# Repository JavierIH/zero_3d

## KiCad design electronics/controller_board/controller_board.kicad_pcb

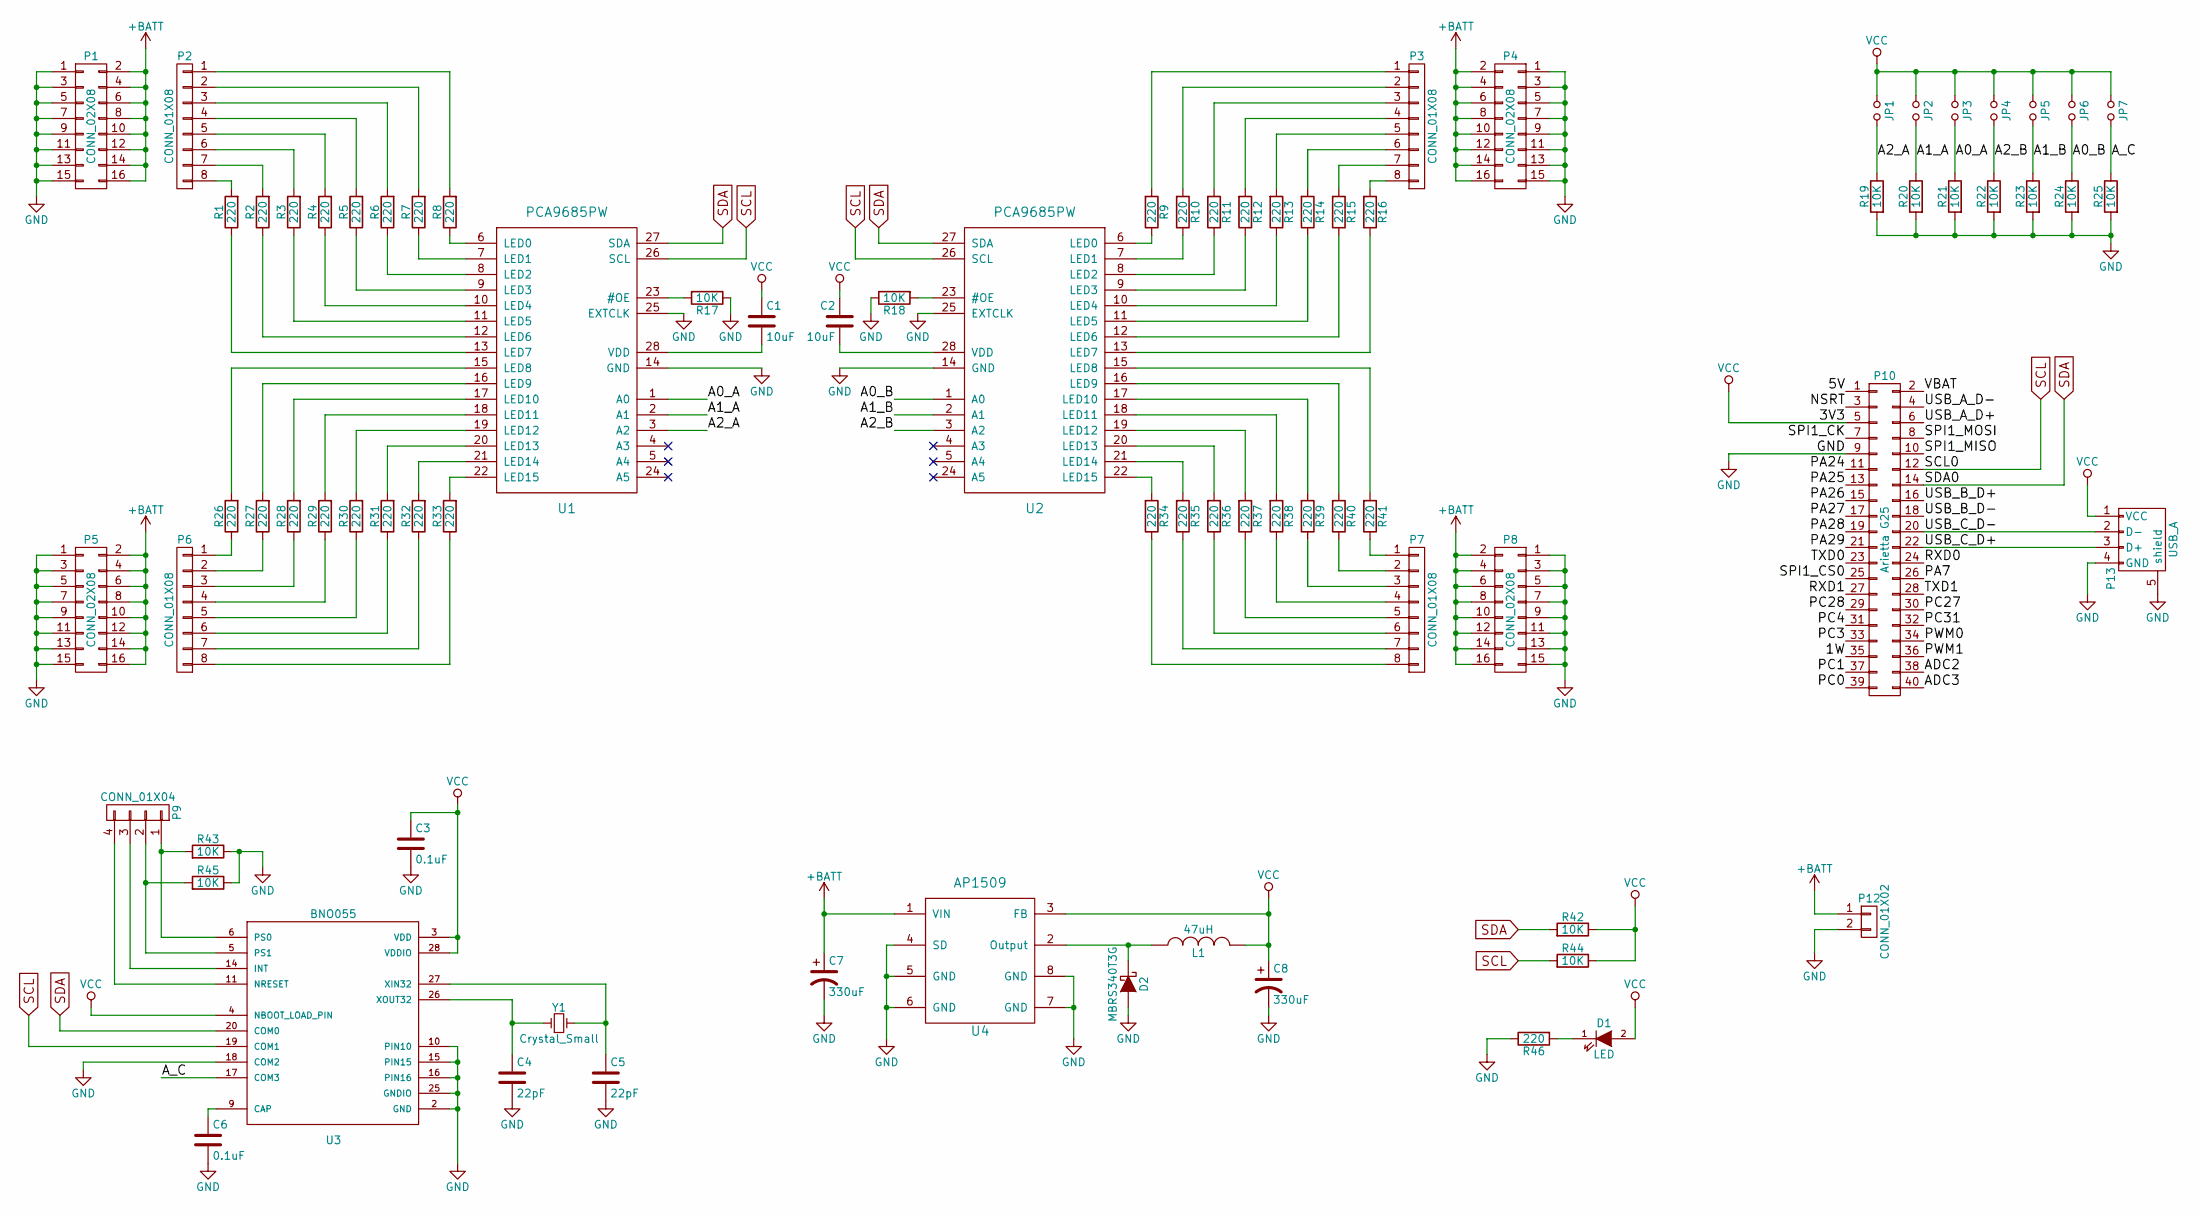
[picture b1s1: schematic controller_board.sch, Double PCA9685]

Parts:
C1, C2: 10uF; C_0603_HandSoldering
C3, C6: 0.1uF; C_0603_HandSoldering
C4, C5: 22pF; C_0603_HandSoldering
C7, C8: 330uF; c_elec_10x10
D1: LED; LED_0603
D2: MBRS340T3G; DO-214AB_Handsoldering
JP1, JP2, JP3, JP4, JP5, JP6, JP7: Jumper_NO_Small; TantalC_SizeS_EIA-3216
L1: 47uH; Choke_SMD_12x12mm_h8mm
P1, P4, P5, P8: CONN_02X08; Pin_Header_Straight_2x08
P2, P3, P6, P7: CONN_01X08; Pin_Header_Straight_1x08
P9: CONN_01X04; Pin_Header_Straight_1x04
P10: Arietta G25; Pin_Header_Straight_2x20
P12: CONN_01X02; Pin_Header_Straight_1x02
P13: USB_A; USB_A_Vertical
R1, R2, R3, R4, R5, R6, R7, R8, R9, R10, R11, R12, R13, R14, R15, R16, R26, R27, R28, R29, R30, R31, R32, R33, R34, R35, R36, R37, R38, R39, R40, R41, R46: 220; R_0603_HandSoldering
R17, R18, R19, R20, R21, R22, R23, R24, R25, R42, R43, R44, R45: 10K; R_0603_HandSoldering
U1, U2: PCA9685PW; TSSOP-28_4.4x9.7mm_Pitch0.65mm
U3: BNO055; DFN-18-1EP_4x5mm_Pitch0.5mm
U4: AP1509; SOIC-8_3.9x4.9mm_Pitch1.27mm
Y1: Crystal_Small; Crystal_HC49-SD_SMD

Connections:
+BATT: C7.1, P1.2, P1.4, P1.6, P1.8, P1.10, P1.12, P1.14, P1.16, P4.2, P4.4, P4.6, P4.8, P4.10, P4.12, P4.14, P4.16, P5.2, P5.4, P5.6, P5.8, P5.10, P5.12, P5.14, P5.16, P8.2, P8.4, P8.6, P8.8, P8.10, P8.12, P8.14, P8.16, P12.1, U4.1 (VIN)
/1W: P10.35
/5V: P10.1
/A0_A: JP3.2, R21.1, U1.1 (A0)
/A0_B: JP6.2, R24.1, U2.1 (A0)
/A1_A: JP2.2, R20.1, U1.2 (A1)
/A1_B: JP5.2, R23.1, U2.2 (A1)
/A2_A: JP1.2, R19.1, U1.3 (A2)
/A2_B: JP4.2, R22.1, U2.3 (A2)
/ADC2: P10.38
/ADC3: P10.40
/A_C: JP7.2, R25.1, U3.17 (COM3)
/NSRT: P10.3
/PA7: P10.26
/PA24: P10.11
/PA25: P10.13
/PA26: P10.15
/PA27: P10.17
/PA28: P10.19
/PA29: P10.21
/PC0: P10.39
/PC1: P10.37
/PC3: P10.33
/PC4: P10.31
/PC27: P10.30
/PC28: P10.29
/PC31: P10.32
/PWM0: P10.34
/PWM1: P10.36
/RXD0: P10.24
/RXD1: P10.27
/SPI1_CK: P10.7
/SPI1_CS0: P10.25
/SPI1_MISO: P10.10
/SPI1_MOSI: P10.8
/TXD0: P10.23
/TXD1: P10.28
/USB_A_D+: P10.6
/USB_A_D-: P10.4
/USB_B_D+: P10.16
/USB_B_D-: P10.18
/USB_C_D+: P10.22, P13.3 (D+)
/USB_C_D-: P10.20, P13.2 (D-)
/VBAT: P10.2
GND: C3.2, C4.2, C5.2, C6.2, C7.2, C8.2, D2.2 (A), P1.1, P1.3, P1.5, P1.7, P1.9, P1.11, P1.13, P1.15, P4.1, P4.3, P4.5, P4.7, P4.9, P4.11, P4.13, P4.15, P5.1, P5.3, P5.5, P5.7, P5.9, P5.11, P5.13, P5.15, P8.1, P8.3, P8.5, P8.7, P8.9, P8.11, P8.13, P8.15, P10.9, P12.2, P13.4 (GND), P13.5 (shield), R17.1, R18.1, R19.2, R20.2, R21.2, R22.2, R23.2, R24.2, R25.2, R43.1, R45.1, R46.1, U1.14 (GND), U1.25 (EXTCLK), U2.14 (GND), U2.25 (EXTCLK), U3.2 (GND), U3.10 (PIN10), U3.15 (PIN15), U3.16 (PIN16), U3.18 (COM2), U3.25 (GNDIO), U4.4 (SD), U4.5 (GND), U4.6 (GND), U4.7 (GND), U4.8 (GND)
unnamed: C1.2, U1.28 (VDD)
unnamed: C2.2, U2.28 (VDD)
unnamed: C4.1, U3.26 (XOUT32), Y1.1
unnamed: C5.1, U3.27 (XIN32), Y1.2
unnamed: C6.1, U3.9 (CAP)
unnamed: D1.1 (K), R46.2
unnamed: D2.1 (K), L1.1, U4.2 (Output)
unnamed: P2.1, R8.2
unnamed: P2.2, R7.2
unnamed: P2.3, R6.2
unnamed: P2.4, R5.2
unnamed: P2.5, R4.2
unnamed: P2.6, R3.2
unnamed: P2.7, R2.2
unnamed: P2.8, R1.2
unnamed: P3.1, R9.2
unnamed: P3.2, R10.2
unnamed: P3.3, R11.2
unnamed: P3.4, R12.2
unnamed: P3.5, R13.2
unnamed: P3.6, R14.2
unnamed: P3.7, R15.2
unnamed: P3.8, R16.2
unnamed: P6.1, R26.1
unnamed: P6.2, R27.1
unnamed: P6.3, R28.1
unnamed: P6.4, R29.1
unnamed: P6.5, R30.1
unnamed: P6.6, R31.1
unnamed: P6.7, R32.1
unnamed: P6.8, R33.1
unnamed: P7.1, R41.1
unnamed: P7.2, R40.1
unnamed: P7.3, R39.1
unnamed: P7.4, R38.1
unnamed: P7.5, R37.1
unnamed: P7.6, R36.1
unnamed: P7.7, R35.1
unnamed: P7.8, R34.1
unnamed: R1.1, U1.13 (LED7)
unnamed: R2.1, U1.12 (LED6)
unnamed: R3.1, U1.11 (LED5)
unnamed: R4.1, U1.10 (LED4)
unnamed: R5.1, U1.9 (LED3)
unnamed: R6.1, U1.8 (LED2)
unnamed: R7.1, U1.7 (LED1)
unnamed: R8.1, U1.6 (LED0)
unnamed: R9.1, U2.6 (LED0)
unnamed: R10.1, U2.7 (LED1)
unnamed: R11.1, U2.8 (LED2)
unnamed: R12.1, U2.9 (LED3)
unnamed: R13.1, U2.10 (LED4)
unnamed: R14.1, U2.11 (LED5)
unnamed: R15.1, U2.12 (LED6)
unnamed: R16.1, U2.13 (LED7)
unnamed: R17.2, U1.23 (#OE)
unnamed: R18.2, U2.23 (#OE)
unnamed: R26.2, U1.15 (LED8)
unnamed: R27.2, U1.16 (LED9)
unnamed: R28.2, U1.17 (LED10)
unnamed: R29.2, U1.18 (LED11)
unnamed: R30.2, U1.19 (LED12)
unnamed: R31.2, U1.20 (LED13)
unnamed: R32.2, U1.21 (LED14)
unnamed: R33.2, U1.22 (LED15)
unnamed: R34.2, U2.22 (LED15)
unnamed: R35.2, U2.21 (LED14)
unnamed: R36.2, U2.20 (LED13)
unnamed: R37.2, U2.19 (LED12)
unnamed: R38.2, U2.18 (LED11)
unnamed: R39.2, U2.17 (LED10)
unnamed: R40.2, U2.16 (LED9)
unnamed: R41.2, U2.15 (LED8)
SCL: P10.12, R44.2, U1.26 (SCL), U2.26 (SCL), U3.19 (COM1)
SDA: P10.14, R42.2, U1.27 (SDA), U2.27 (SDA), U3.20 (COM0)
VCC: C1.1, C2.1, C3.1, C8.1, D1.2 (A), JP1.1, JP2.1, JP3.1, JP4.1, JP5.1, JP6.1, JP7.1, L1.2, P10.5, P13.1 (VCC), R42.1, R44.1, U3.3 (VDD), U3.4 (NBOOT_LOAD_PIN), U3.28 (VDDIO), U4.3 (FB)

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
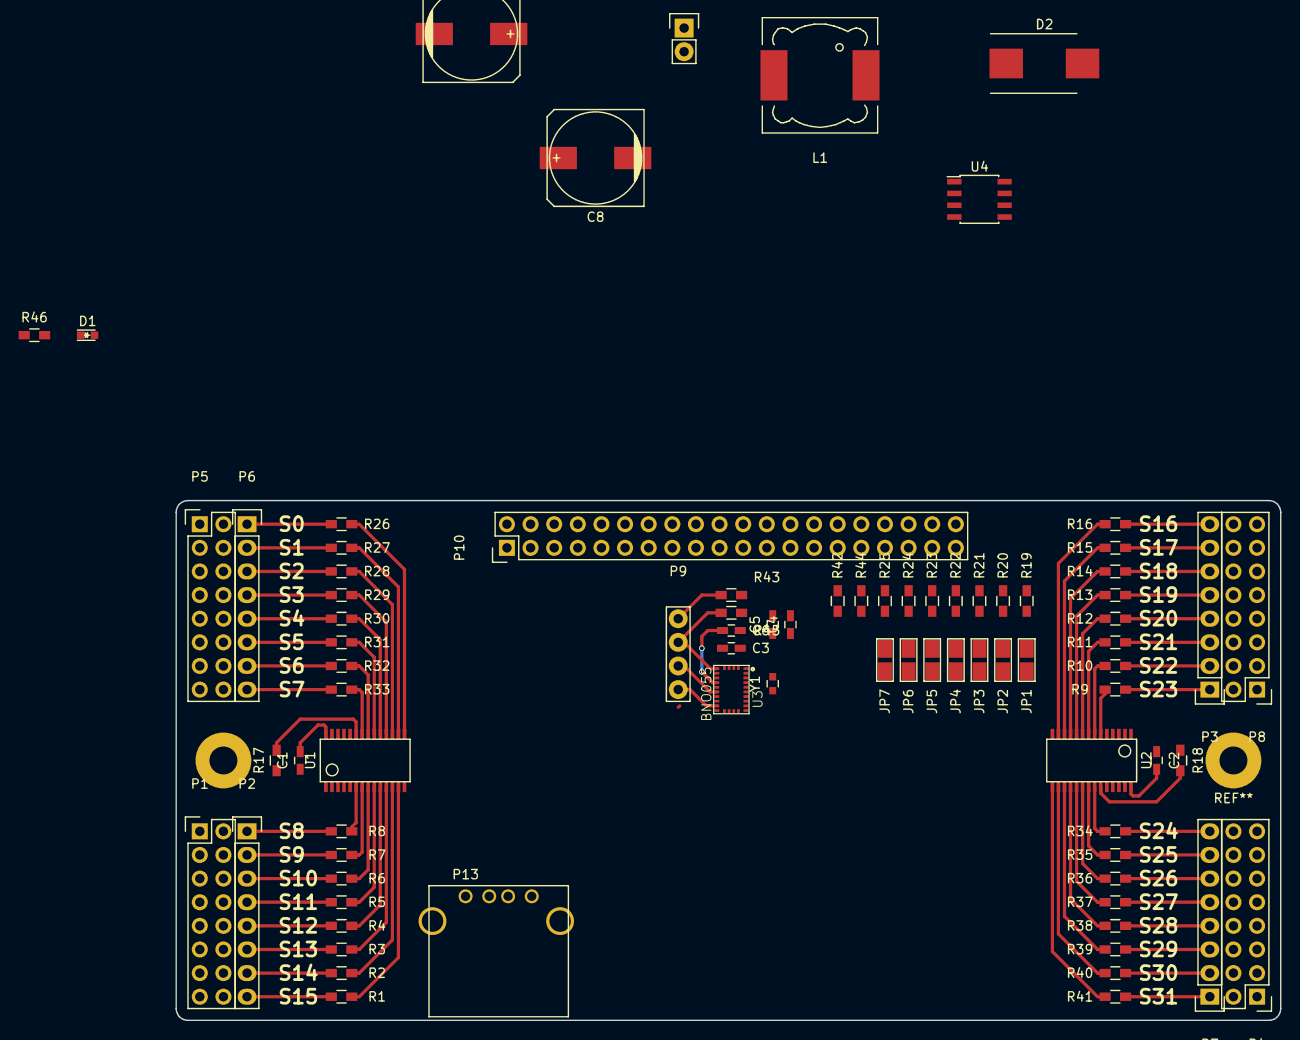
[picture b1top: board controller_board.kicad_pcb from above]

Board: 2 copper layers, 118.7 x 55.9 mm, 82 parts (0 on the bottom side), 91 nets.

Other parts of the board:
m3: Hole_3mm

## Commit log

2016-02-15 3d model
2016-02-18 updated design
2016-02-25 updated legs
2016-03-30 last commit
2016-10-14 new body parts
2016-10-14 controller board sources
2016-10-15 add bno055 in controller board
2016-10-15 arietta socket, led, i2c pull up resistor...
2016-10-28 place some components on PCB
2016-10-31 More routing on board
